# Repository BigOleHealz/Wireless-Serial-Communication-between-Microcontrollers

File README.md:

# **Introduction**

The purpose of this project is to wire a MDBT40 chip to wirelessly communicate with a MK20DX256VHL7 Cortex-M4 via Bluetooth 4.2, with the MK20 acting as the receiver ready to scroll text across an LED display while the MDBT40 acts as the remote writing characteristics to the receiver. To accomplish this, the MK20 is outfitted with a BT840 chip to handle Bluetooth communication.

In addition to the dedicated remote, a Bluetooth-enabled smart phone can be used to control the MK20 via our Android app. 

# **Usage**

### Mobile App
The app itself is rather intuitive. Upon first opening the app, the user will be shown a list of all device names within range that have a UUID matching one of the UUIDs in our predefined library. The predefined library ensures that the user will only be shown devices with BT840 chips with our software installed on them. At the time of pairing, the user's device will most likely be the only one within range so finding their device should be very straightforward. If another device is within range, the user may need to sort through the list to find theirs. The user only needs to complete this process once as the UUID of their device will be saved in the app for future use. After this, the phone will automatically connect to the BT840 chip upon launching of the app.

While connected, the user can send a message to the MK20 simply by tapping any of the buttons at the four corners of the screen. Obviously, the message sent will match the text on the button. The button text can be manually changed by long-pressing on the button itself, which clears the text from the button and raises the keyboard. 

In addition, voice functionality is available in the app by tapping the center button. If the message sends successfully, the car icon at the top of the display will zoom across the screen from right to left. If you do not see the car zoom across the screen, it is due to 1 of 3 reasons: either the mobile device is not properly paired to the display, the text input was determined to be aggressive and/or hostile, or the car raced across the screen so fast that you blinked and missed it.

### Remote
The remote features six buttons corresponding to six preset messages, as well as a central “confirm” or “send” button. It comes with an omni-directional swivel mount which allows users to adhere it to the dashboard or AC vent. It comes pre-paired with with BT840.

When one of the six buttons are pressed, a blue LED ring lights up next to the button to show the user which message has been activated. The user may then press the center button to send the message to the LED display. This 2-step process is designed mostly to prevent the user from accidentally sending the wrong message. Upon activation of the "send" button, the LED ring should sequentially light up blue until the entire ring is illuminated blue. The LEDs next to the activated button will turn to green and then fade away if the message sends successfully. However, they will turn red and fade away if an error was encountered.

### LED Display Board
Hardware installation of the LED display itself is fairly straightforward. Just mount it on your rear windshield by rotating the side panels 180° so that both suction cups face the same direction as the display. Simply place the suction cups against the inside of the rear windshield and lock the flaps on the opposite face of the panels. Then flip the switch on the rear of the enclosure to power on the device.

When the display board receives a message, it will display it for a maximum of 7 seconds so as not to distract the rear driver. However, the message will scroll faster for longer messages so that the rear driver gets to see the message twice before it disappears in case they missed it the first time.

# **Functionality**

### BT840
Using the BLEPeripheral, the BT840 is declared as a BLEPeripheral device named "peripheral" having BLEService named "service" with the UUID "19b11234e8f2537e4f6cd104768a1214" and a BLECharacteristic named "characteristic" with UUID "19b10000e8f2537e4f6cd104768a1214". Next, the advertisement UUID for peripheral is set to the UUID of service, the default value of characteristic is set to "BLE Character", and the device's local name is set to "BLE Device". Finally, we call Wire.begin() so that we can communicate with the MK20 via I2C.

In the loop() function a BLECentral named "other_device" is instantiated as a central to peripheral for each loop executed until a central is connected. While connected, LED_BUILTIN will light up and the BT840 will wait for the user to overwrite the value of characteristic. If overwritten, the string value of characteristic is converted into a char array and sent byte-by-byte to the MK20 via I2C over channel 9.

### MK20DX256VHL7
The script begins by setting all constants like the matrix height and width as well as instantiating an Adafruit_LIS3DH object named "lis". The Adafruit_LIS3DH library is for use with 3-axis accelerometers and present in this skit so that the text will scroll from right to left regardless of orientation. 

In the setup() function, a scrolling layer is added to the matrix so that the color, scroll speed, font size, etc. of the text can be customized. Constant settings are then set for matrix and scrollingLayer. Wire1 is instantiated on channel 9 to receive data from the BT840 (Wire1 because Wire is occupied by the accelerometer). Finally, the callback method receiveEvent is passed to Wire1.onReceive() to be executed any time the MK20 receives data from the BT840.

In loop() we simply call the setRotation() function which reads input from the accelerometer and sets the rotation accordingly, so that the text is right-side-up and scrolls from right to left.

# **Features**
The mobile app blocks any inflammatory statements from being sent to the board. It does so using an exhaustive library of aggressive and/or hostile terms stored locally on the app. This library includes everything from benign but negative adjectives like “dumb” and “stupid”, to curse words, to homophobic and racial slurs… The is NO reason drivers should need these words while trying to de-escalate aggressive situations. 

The app also features Google’s voice recognition software, allowing drivers to operate the device while keeping both hands on the wheel and their eyes on the road. Again, the voice functionality will flag any aggressive or inflammatory messages.

# **Required Software, Hardware, & Wiring**
### Arduino Libraries Required

* [NeoPixel](https://github.com/adafruit/Adafruit_NeoPixel)
* [SmartMatrix3](https://github.com/pixelmatix/SmartMatrix)
* [Software Serial](https://github.com/PaulStoffregen/SoftwareSerial)
* [BLEPeripheral](https://github.com/sandeepmistry/arduino-BLEPeripheral)
* [Wire](https://github.com/esp8266/Arduino/tree/master/libraries/Wire)
* [Adafruit_LIS3DH](https://github.com/adafruit/Adafruit_LIS3DH)
* [Adafruit_Sensor](https://github.com/adafruit/Adafruit_Sensor)

### Components Required
* [Teensy 3.2]( https://www.pjrc.com/store/teensy32.html)
* [nRF52832 Development Kit](https://www.nordicsemi.com/eng/Products/Bluetooth-low-energy/nRF52-DK)

* 2 x [64 x 32 LED Matrices](https://www.adafruit.com/product/2278)
* 2 x [TP4056 Charging Module](https://www.amazon.com/McIgIcM-Lithium-Charging-Protection-Functions/dp/B06XQRQR3Q/ref=sr_1_1_sspa?s=electronics&ie=UTF8&qid=1521743259&sr=1-1-spons&keywords=tp4056+charging+module&psc=1)
* [LM2596 XL6009](https://www.amazon.com/gp/product/B0129HYAW0/ref=oh_aui_search_detailpage?ie=UTF8&psc=1)
* 2 x [10uF Polarized Capacitor](https://www.amazon.com/uxcell-10uF-Radial-Electrolytic-Capacitor/dp/B00W8YAJ2A/ref=sr_1_3?s=electronics&ie=UTF8&qid=1521743487&sr=1-3&keywords=10uf+capacitor)
* [LiPo Battery - 4000mAh](https://www.amazon.com/Ofeely-4000mah-Polymer-Battery-Rechargeable/dp/B00U8GFKR4)
* [LiPo Battery - 500 mAh](https://www.amazon.com/ADAFRUIT-INDUSTRIES-1578-Lithium-Polymer/dp/B00L0W61VO/ref=sr_1_5?ie=UTF8&qid=1521839930&sr=8-5&keywords=battery+500mah)
* [16-Pin Ribbon Cable](https://www.amazon.com/Pc-Accessories-Connectors-2-Pack-Silver/dp/B01J4NN9LK/ref=sr_1_11?s=electronics&ie=UTF8&qid=1522098852&sr=1-11&keywords=16+pin+ribbon+cable)
* [12 LED NeoPixel Ring](https://www.amazon.com/Pc-Accessories-Connectors-2-Pack-Silver/dp/B01J4NN9LK/ref=sr_1_11?s=electronics&ie=UTF8&qid=1522098852&sr=1-11&keywords=16+pin+ribbon+cable)
* 7 x [Buttons](https://www.amazon.com/OCR-Tactile-Button-Momentary-Assortment/dp/B01MRP025V/ref=sr_1_1?ie=UTF8&qid=1521743850&sr=8-1&keywords=electronic+buttons)

# **Remote/Transmitter:**

# **Receiver:**

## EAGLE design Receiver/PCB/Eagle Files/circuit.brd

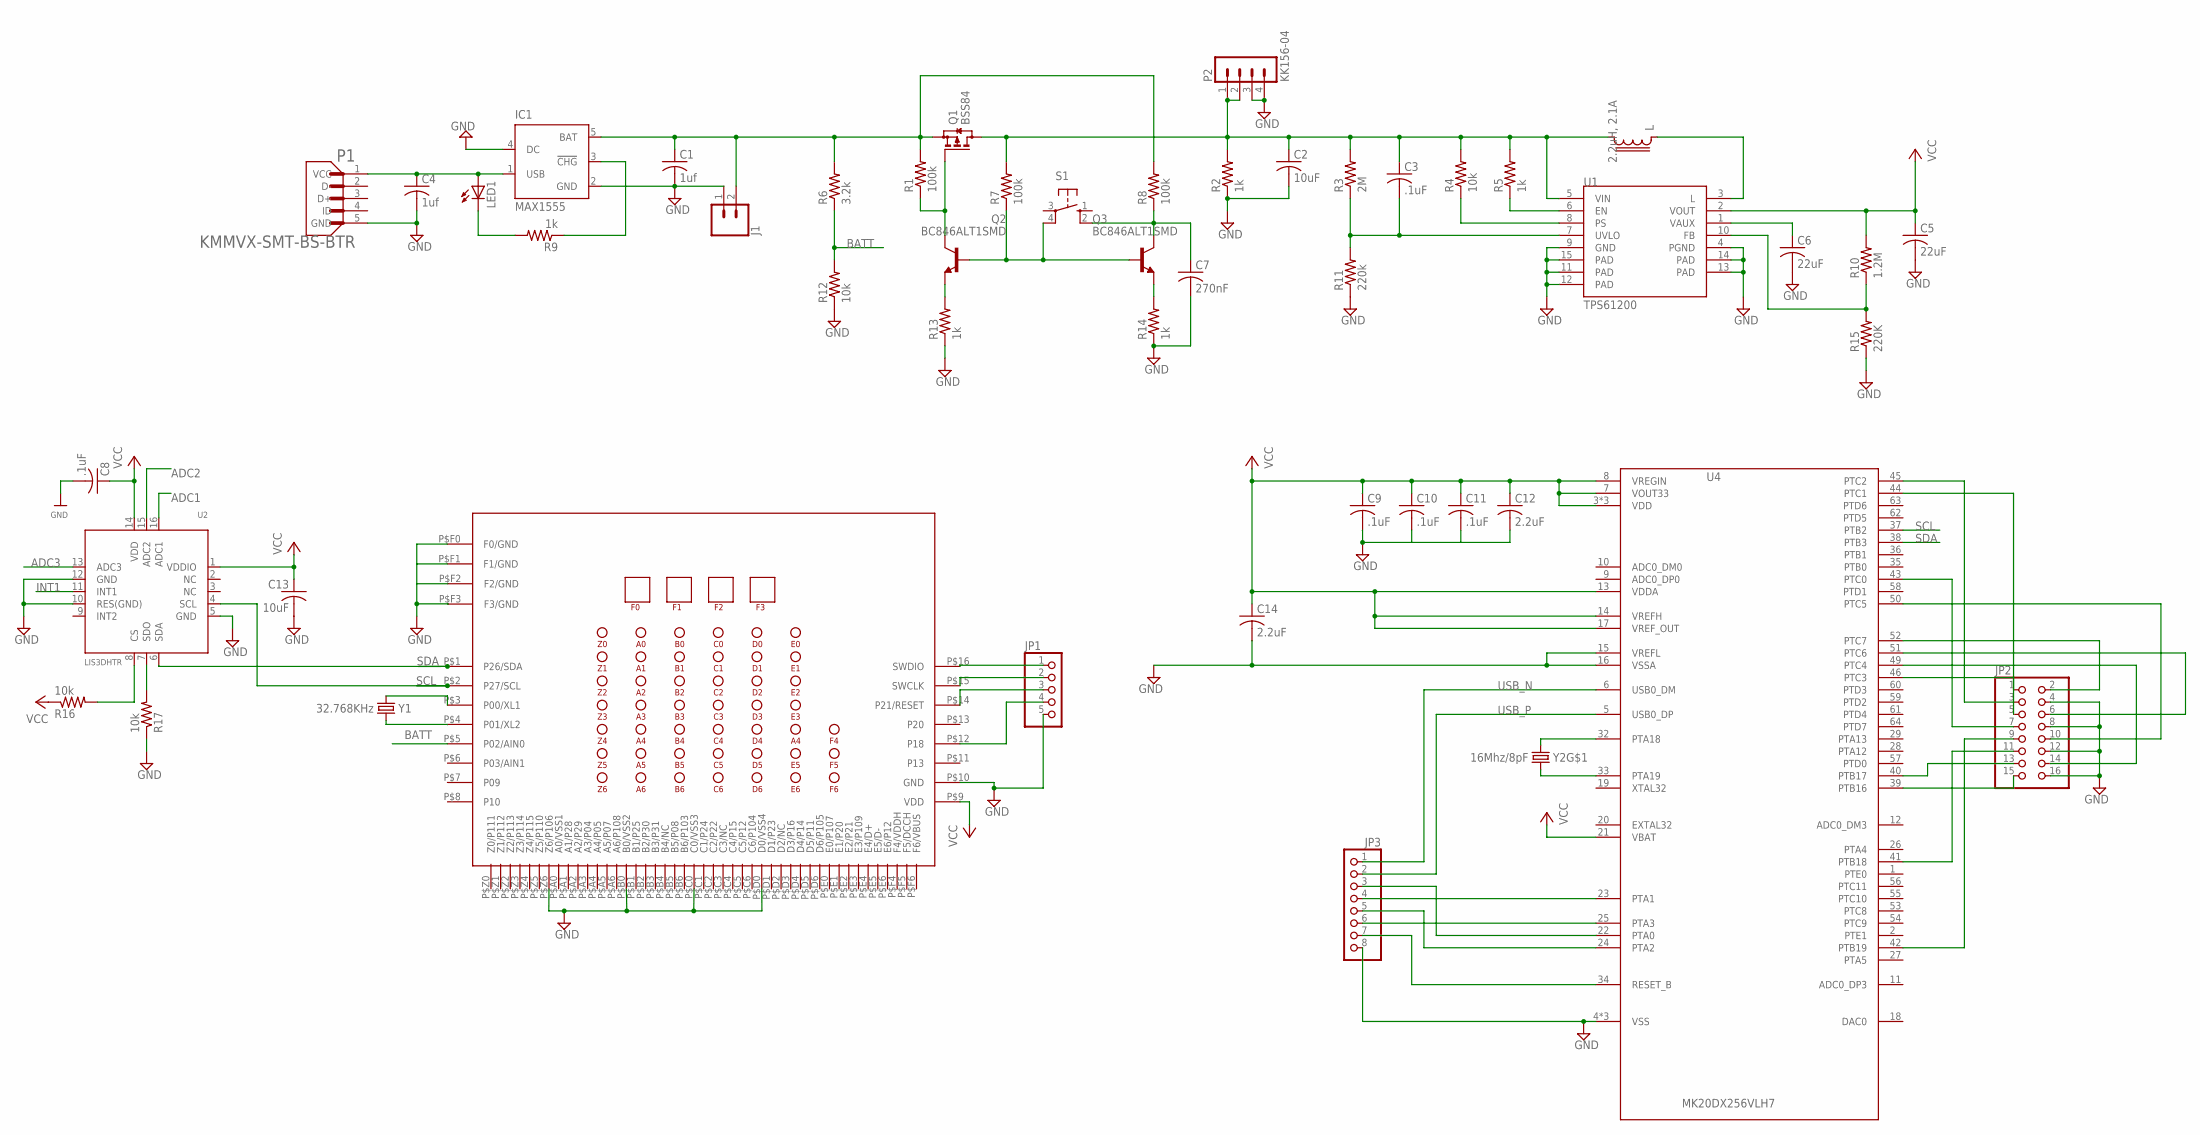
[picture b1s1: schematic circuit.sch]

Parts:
C1, C4: 1uf; C0402
C2, C13: 10uF; C0402
C3, C8, C9, C10, C11: .1uF; C0402
C5, C6: 22uF; C0402
C7: 270nF; C0402; MPN C1206C274K1RACTU
C12, C14: 2.2uF; C0402
IC1: MAX1555; SOT23-5L
J1: CONN_02-JST-2-PTH-NO_SILK; JST-2-PTH-NS
JP1: PINHD-1X5; 1X05
JP2: PINHD-2X8; 2X08
JP3: PINHD-1X8; 1X08
L: 2.2uH, 2.1A; LPS3015
LED1: LEDSML0805; SML0805
P1: KMMVX-SMT-BS-BTR; KYCON_KMMVX-SMT-BS-BTR
P2: KK156-04
Q1: BSS84; SOT23
Q2, Q3: BC846ALT1SMD; SOT23
R1, R7, R8: 100k; R0402
R2, R5, R9, R13, R14: 1k; R0402
R3: 2M; R0402
R4, R12, R16, R17: 10k; R0402
R6: 3.2k; R0402
R10: 1.2M; R0402
R11: 220k; R0402
R15: 220K; R0402
S1: 10-XX; B3F-10XX
U1: TPS61200; QFN-10_PAD
U2: LIS3DHTR; LGA16_3X3MM
U3: BT840
U4: MK20DX256VLH7
Y1: 32.768KHz; CRYSTAL-TXC-7A
Y2: 16Mhz/8pF; CRYSTAL-SMD-5X3

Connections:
ADC1: U2.16 (ADC1)
ADC2: U2.15 (ADC2)
ADC3: U2.13 (ADC3)
BATT: R6.1, R12.2, U3.P$5 (P02/AIN0)
GND: C1.2, C2.2, C4.2, C5.2, C6.2, C7.2, C8.2, C9.2, C10.2, C13.2, C14.2, IC1.2 (GND), IC1.4 (DC), J1.1, JP1.5, JP2.4, JP2.8, JP2.12, JP2.16, JP3.8, P1.5 (GND), P2.3, P2.4, R2.1, R11.1, R12.1, R13.1, R14.1, R15.1, R17.1, U1.4 (PGND), U1.9 (GND), U1.11 (PAD), U1.12 (PAD), U1.13 (PAD), U1.14 (PAD), U1.15 (PAD), U2.5 (GND), U2.10 (RES(GND)), U2.12 (GND), U3.P$10 (GND), U3.P$B0 (B0/VSS2), U3.P$C0 (C0/VSS3), U3.P$D0 (D0/VSS4), U3.P$F0 (F0/GND), U3.P$F1 (F1/GND), U3.P$F2 (F2/GND), U3.P$F3 (F3/GND), U3.P$Z6 (Z6/P106), U4.4 (VSS), U4.15 (VREFL), U4.16 (VSSA), U4.31 (VSS), U4.47 (VSS)
GND1: C11.2
GND2: C12.2
INT1: U2.11 (INT1)
unnamed: Q1.1 (G), Q2.3 (C), R1.1
unnamed: C7.1, Q3.3 (C), R8.1, S1.2 (S1)
unnamed: Q2.2 (E), R13.2
unnamed: Q2.1 (B), Q3.1 (B), R7.1, S1.4 (P1)
unnamed: Q3.2 (E), R14.2
unnamed: JP2.1, U4.46 (PTC3)
unnamed: U3.P$3 (P00/XL1), Y1.P$2 (2)
unnamed: C4.1, IC1.1 (USB), LED1.A, P1.1 (VCC)
unnamed: R16.2, U2.8 (CS)
unnamed: IC1.3 (!CHG), R9.1
unnamed: LED1.C, R9.2
unnamed: R17.2, U2.7 (SDO)
unnamed: L.1, U1.3 (L)
unnamed: JP3.3, U4.22 (PTA0)
unnamed: U3.P$4 (P01/XL2), Y1.P$1 (1)
unnamed: C3.2, R3.1, R11.2, U1.7 (UVLO)
unnamed: R4.1, U1.8 (PS)
unnamed: JP3.4, U4.23 (PTA1)
unnamed: R5.1, U1.6 (EN)
unnamed: C6.1, U1.1 (VAUX)
unnamed: JP3.5, U4.24 (PTA2)
unnamed: R10.1, R15.2, U1.10 (FB)
unnamed: JP3.6, U4.25 (PTA3)
unnamed: JP3.7, U4.34 (RESET_B)
unnamed: JP1.1, U3.P$16 (SWDIO)
unnamed: JP1.2, U3.P$15 (SWCLK)
unnamed: U4.32 (PTA18), Y2.3 (2)
unnamed: U4.33 (PTA19), Y2.1
unnamed: JP1.3, U3.P$14 (P21/RESET)
unnamed: JP1.4, U3.P$12 (P18)
unnamed: C1.1, IC1.5 (BAT), J1.2, Q1.2 (S), R1.2, R6.2, R8.2
unnamed: JP2.3, U4.45 (PTC2)
unnamed: JP2.5, U4.44 (PTC1)
unnamed: JP2.7, U4.43 (PTC0)
unnamed: JP2.9, U4.42 (PTB19)
unnamed: JP2.11, U4.41 (PTB18)
unnamed: JP2.13, U4.40 (PTB17)
unnamed: JP2.15, U4.39 (PTB16)
unnamed: JP2.14, U4.49 (PTC4)
unnamed: JP2.10, U4.50 (PTC5)
unnamed: JP2.6, U4.51 (PTC6)
unnamed: JP2.2, U4.52 (PTC7)
SCL: U2.4 (SCL), U3.P$2 (P27/SCL), U4.37 (PTB2)
SDA: U2.6 (SDA), U3.P$1 (P26/SDA), U4.38 (PTB3)
USB_N: JP3.1, U4.6 (USB0_DM)
USB_P: JP3.2, U4.5 (USB0_DP)
VCC: C5.1, C8.1, C9.1, C10.1, C11.1, C12.1, C13.1, C14.1, R10.2, R16.1, U1.2 (VOUT), U2.1 (VDDIO), U2.14 (VDD), U3.P$9 (VDD), U4.3 (VDD), U4.7 (VOUT33), U4.8 (VREGIN), U4.13 (VDDA), U4.14 (VREFH), U4.17 (VREF_OUT), U4.21 (VBAT), U4.30 (VDD), U4.48 (VDD)
VIN: C2.1, C3.1, L.2, P2.1, P2.2, Q1.3 (D), R2.2, R3.2, R4.2, R5.2, R7.2, U1.5 (VIN)

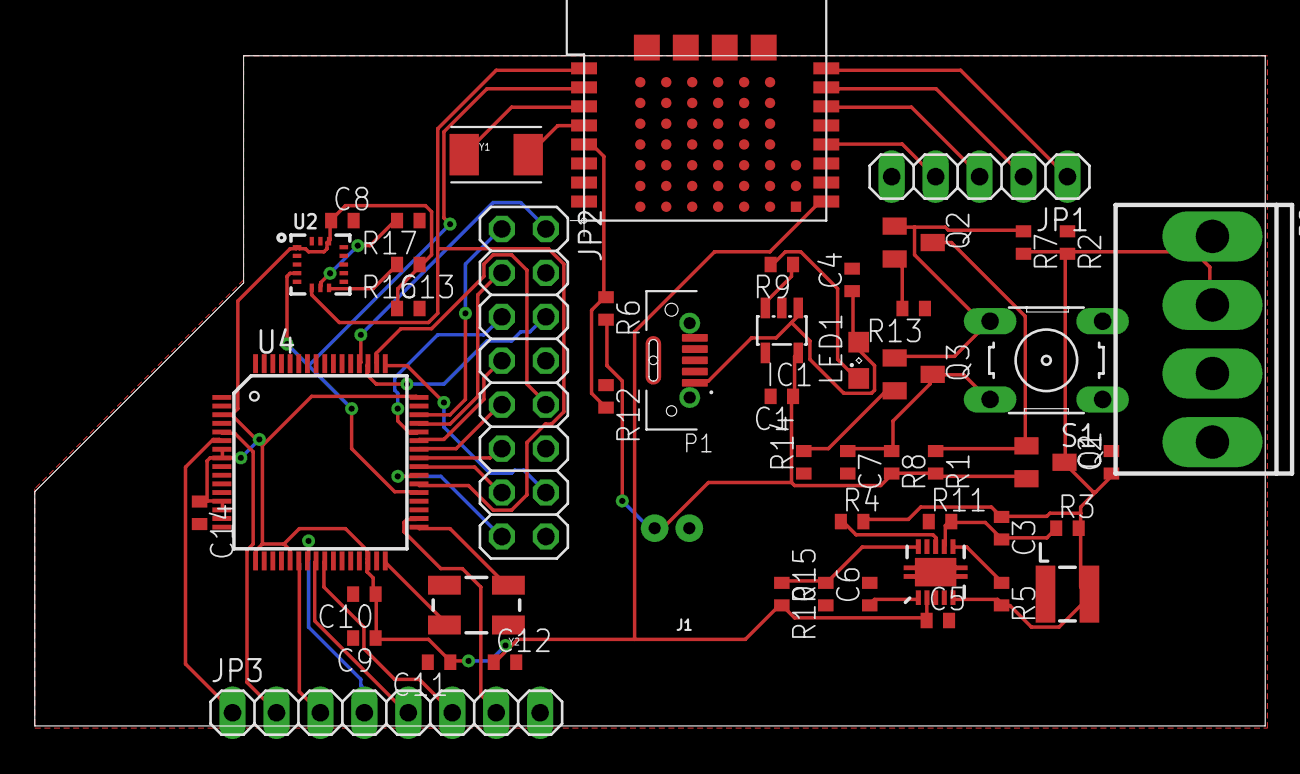
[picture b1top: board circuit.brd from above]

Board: 2 copper layers, 71.1 x 38.7 mm, 50 parts (0 on the bottom side), 50 nets.

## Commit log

2018-03-14 :boom::camel: Added .gitattributes & .gitignore files
2018-03-14 App, Codes, PCB, Schematic, & Screenshots
    Android app, Fritzing and Gerber files, Microcontroller codes,
    Screenshots of breadboard diagram, schematic, PCB, and physical
    prototype
2018-03-26 Added README.md file
    Updated some of the pictures, but mostly just added the README.md
2018-03-26 Updated README.md
    Updated README.md
2018-03-26 Playing with README format
    Playing with README format
2018-03-26 Changing README.md back
    Changing README.md back
2018-05-08 5-8-2018
    Update README.md, Delete extra HTML files, Tidy up images
2018-05-08 Testing README Images
2018-05-08 Updating README images & Consolidating folders
2018-05-08 Updating Image Files
2018-09-28 Updated Fritzing Files
2018-10-11 Production Version Summary
    Describes product down to chip level. Includes scripts for BT840 and
    MK20 as well as Eagle .sch and .brd files and gerber files.
    Still needed: MDBT40 Eagle files and scripts
2018-10-11 Formatting & Style
2018-11-21 Minor Changes
2024-10-10 Add a template: bug_report.yml

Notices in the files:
parts and their libraries:
microbuilder: This work is placed in the public domain, and may be freely used for commercial and non-commercial work with the following conditions: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
SparkFun-Connectors: Licensing: Creative Commons ShareAlike 4.0 International - https://creativecommons.org/licenses/by-sa/4.0
